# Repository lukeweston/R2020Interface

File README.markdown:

CAN interface board for Rutex R2020 servo controller   

// Rest of readme goes here.

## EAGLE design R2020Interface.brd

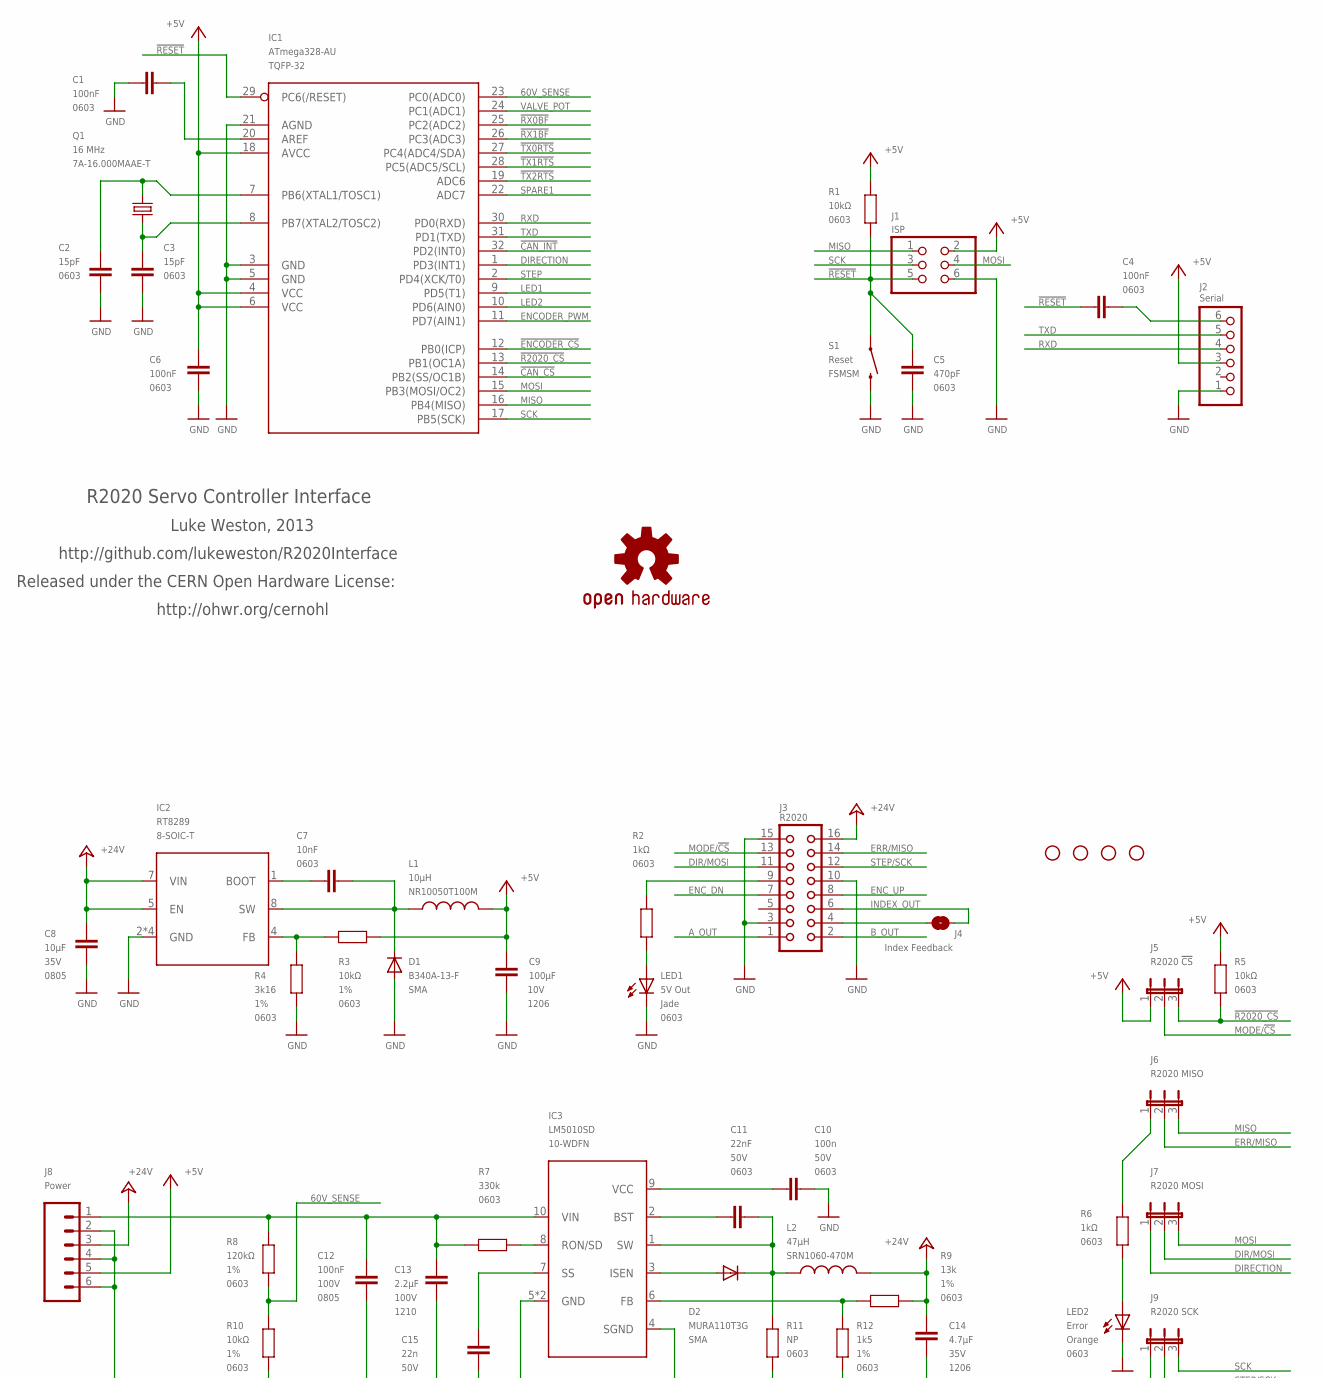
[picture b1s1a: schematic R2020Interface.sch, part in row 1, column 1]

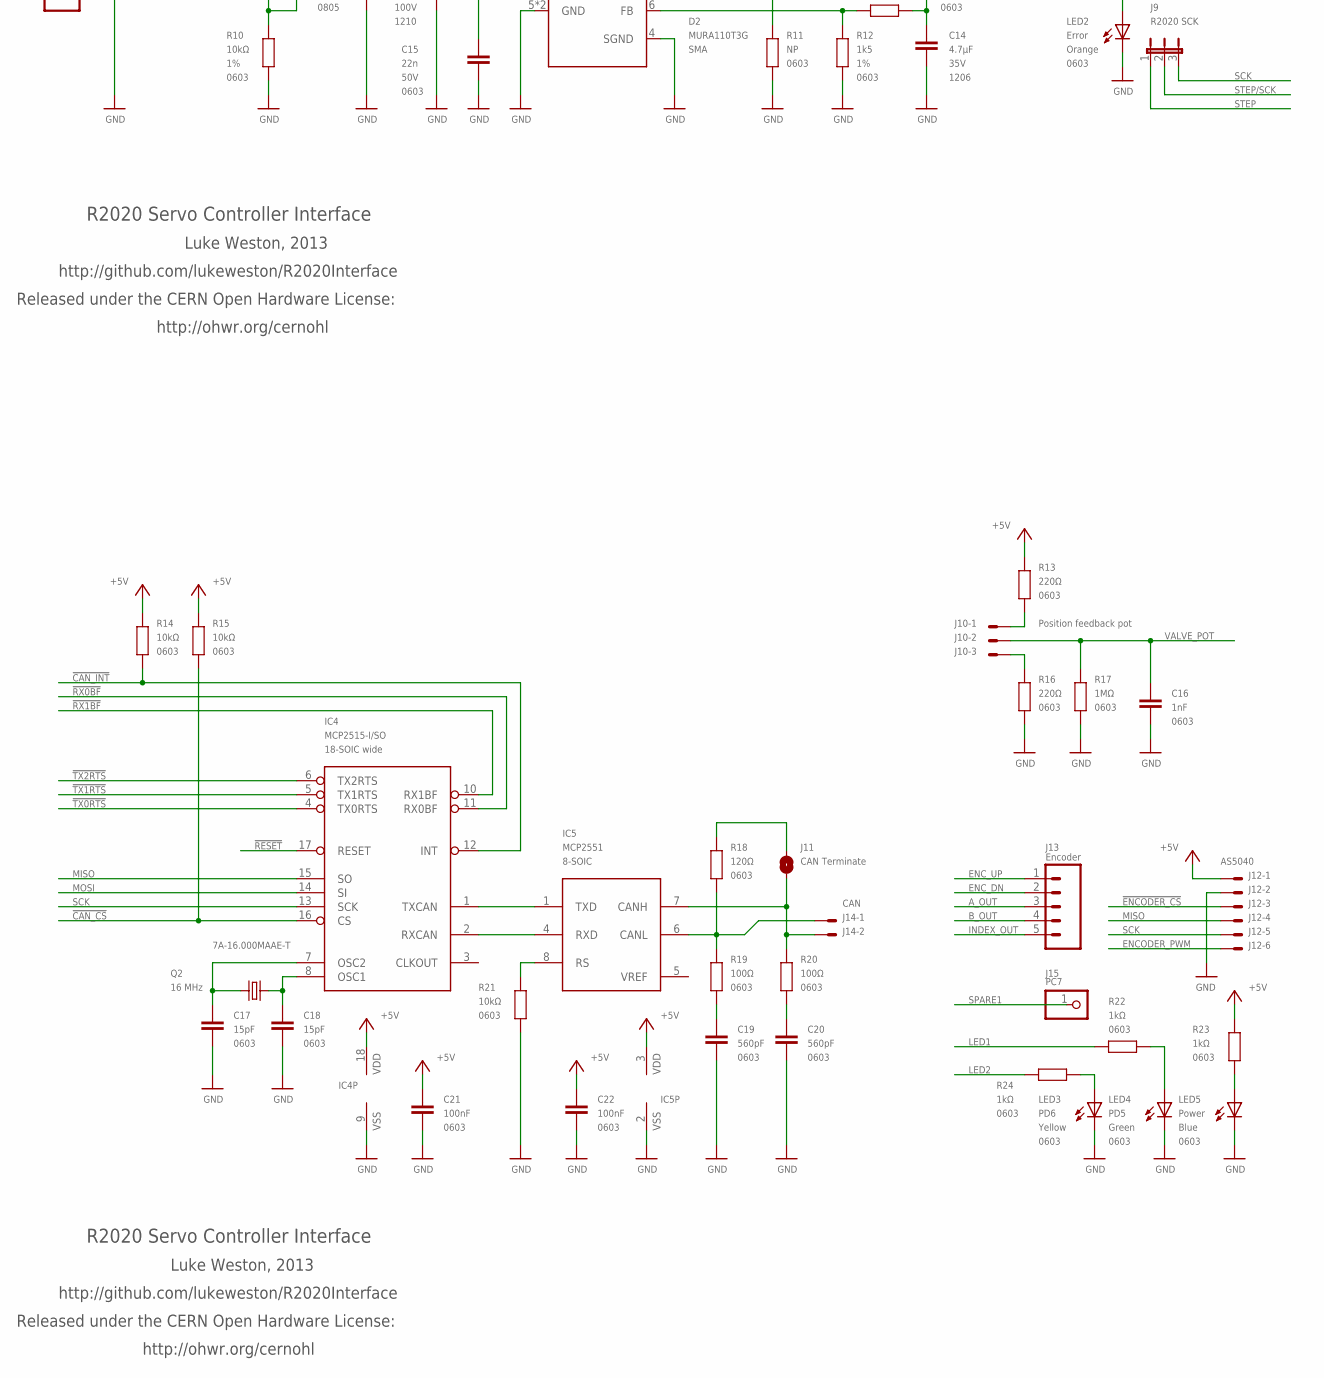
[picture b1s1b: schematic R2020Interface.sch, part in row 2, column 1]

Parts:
C1, C4, C6, C21, C22: 100nF; 0603
C2, C3, C17, C18: 15pF; 0603
C5: 470pF; 0603
C7: 10nF; 0603
C8: 10µF; 0805; VOLTAGE 35V
C9: 100µF; C1206K; VOLTAGE 10V
C10: 100n; 0603; VOLTAGE 50V
C11: 22nF; 0603; VOLTAGE 50V
C12: 100nF; 0805; VOLTAGE 100V
C13: 2.2µF; C1210K; VOLTAGE 100V
C14: 4.7µF; C1206K; VOLTAGE 35V
C15: 22n; 0603; VOLTAGE 50V
C16: 1nF; 0603
C19, C20: 560pF; 0603
D1: B340A-13-F; SMA-DIODE
D2: MURA110T3G; SMA-DIODE
IC1: ATmega328-AU; TQFP32-08
IC2: RT8289; SO08T
IC3: LM5010SD; 10-WSON
IC4: MCP2515-I/SO; SO-18W
IC5: MCP2551; SO-08
J1: ISP; 2X03
J2: Serial; 1X06
J3: R2020; CON16
J4: Index Feedback; SJ
J5: R2020 !CS; JP2
J6: R2020 MISO; JP2
J7: R2020 MOSI; JP2
J8: Power; TERMINALBLOCK_3.5MM_6
J9: R2020 SCK; JP2
J10: Position feedback pot; 7395-03
J11: CAN Terminate; SJ
J12: AS5040; 7395-06
J13: Encoder; 1X05
J14: CAN; 7395-02
J15: PC7; 1X01
JP1, JP2, JP3, JP4: STAND-OFF
L1: 10µH; NR10050
L2: 47µH; SRN1060
LED1: 5V Out; LED-0603
LED2: Error; LED-0603
LED3: PD6; LED-0603
LED4: PD5; LED-0603
LED5: Power; LED-0603
Q1, Q2: 16 MHz; CRYSTAL-3.2X5MM
R1, R5, R14, R15, R21: 10kΩ; 0603
R2, R6, R22, R23, R24: 1kΩ; 0603
R3, R10: 10kΩ; 0603; TOLERANCE 1%
R4: 3k16; 0603; TOLERANCE 1%
R7: 330k; 0603
R8: 120kΩ; 0603; TOLERANCE 1%
R9: 13k; 0603; TOLERANCE 1%
R11: NP; 0603
R12: 1k5; 0603; TOLERANCE 1%
R13, R16: 220Ω; 0603
R17: 1MΩ; 0603
R18: 120Ω; 0603
R19, R20: 100Ω; 0603
S1: Reset; FSMSM
SY1: OSHW-LOGOS; OSHW-LOGO-S

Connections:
60V_SENSE: IC1.23 (PC0(ADC0)), R8.1, R10.2
!CAN_CS: IC1.14 (PB2(SS/OC1B)), IC4.16 (CS), R15.2
!CAN_INT: IC1.32 (PD2(INT0)), IC4.12 (INT), R14.2
!ENCODER_CS: IC1.12 (PB0(ICP)), J12.3
!R2020_CS: IC1.13 (PB1(OC1A)), J5.3, R5.2
!RESET: C4.1, C5.2, IC1.29 (PC6(/RESET)), IC4.17 (RESET), J1.5, R1.1, S1.1
!RX0BF: IC1.25 (PC2(ADC2)), IC4.11 (RX0BF)
!RX1BF: IC1.26 (PC3(ADC3)), IC4.10 (RX1BF)
!TX0RTS: IC1.27 (PC4(ADC4/SDA)), IC4.4 (TX0RTS)
!TX1RTS: IC1.28 (PC5(ADC5/SCL)), IC4.5 (TX1RTS)
!TX2RTS: IC1.19 (ADC6), IC4.6 (TX2RTS)
+5V: C6.1, C9.1, C21.2, C22.2, IC1.4 (VCC), IC1.6 (VCC), IC1.18 (AVCC), IC4.18 (VDD), IC5.3 (VDD), J1.2, J2.3, J5.1, J8.5, J12.1, L1.2, R1.2, R3.1, R5.1, R13.1, R14.1, R15.1, R23.1
+24V: C8.2, C14.1, IC2.5 (EN), IC2.7 (VIN), J3.16, J8.3, L2.2, R9.1
A_OUT: J3.1, J13.3
B_OUT: J3.2, J13.4
DIR/MOSI: J3.11, J7.2
DIRECTION: IC1.1 (PD3(INT1)), J7.1
ENCODER_PWM: IC1.11 (PD7(AIN1)), J12.6
ENC_DN: J3.7, J13.2
ENC_UP: J3.8, J13.1
ERR/MISO: J3.14, J6.2
GND: C1.2, C2.1, C3.1, C5.1, C6.2, C8.1, C9.2, C10.1, C12.1, C13.2, C14.2, C15.1, C16.1, C17.1, C18.1, C19.1, C20.1, C21.1, C22.1, D1.A, IC1.3 (GND), IC1.5 (GND), IC1.21 (AGND), IC2.2 (GND), IC2.3 (GND), IC2.6 (GND), IC2.PAD (GND), IC3.4 (SGND), IC3.5 (GND), IC3.PAD (GND), IC4.9 (VSS), IC5.2 (VSS), J1.6, J2.1, J3.3, J3.10, J3.15, J8.2, J8.4, J8.6, J12.2, LED1.C, LED2.C, LED3.C, LED4.C, LED5.C, R4.1, R10.1, R11.2, R12.1, R16.2, R17.2, R21.2, S1.2
INDEX_IN: J3.4, J4.2
INDEX_OUT: J3.6, J4.1, J13.5
LED1: IC1.9 (PD5(T1)), R22.2
LED2: IC1.10 (PD6(AIN0)), R24.2
MISO: IC1.16 (PB4(MISO)), IC4.15 (SO), J1.1, J6.3, J12.4
MODE/!CS: J3.13, J5.2
MOSI: IC1.15 (PB3(MOSI/OC2)), IC4.14 (SI), J1.4, J7.3
unnamed: C1.1, IC1.20 (AREF)
unnamed: C2.2, IC1.7 (PB6(XTAL1/TOSC1)), Q1.1
unnamed: C3.2, IC1.8 (PB7(XTAL2/TOSC2)), Q1.2
unnamed: LED1.A, R2.1
unnamed: J3.9, R2.2
unnamed: J10.1, R13.2
unnamed: J6.1, R6.1
unnamed: J11.2, R18.1
unnamed: J10.3, R16.1
unnamed: LED2.A, R6.2
unnamed: C7.1, D1.C, IC2.8 (SW), L1.1
unnamed: IC5.7 (CANH), J11.1, J14.2, R20.1
unnamed: LED3.A, R24.1
unnamed: IC2.4 (FB), R3.2, R4.2
unnamed: LED4.A, R22.1
unnamed: C7.2, IC2.1 (BOOT)
unnamed: C11.1, D2.C, IC3.1 (SW), L2.1, R11.1
unnamed: IC5.8 (RS), R21.1
unnamed: D2.A, IC3.3 (ISEN)
unnamed: IC3.6 (FB), R9.2, R12.2
unnamed: C15.2, IC3.7 (SS)
unnamed: IC3.8 (RON/SD), R7.1
unnamed: IC4.2 (RXCAN), IC5.4 (RXD)
unnamed: IC4.1 (TXCAN), IC5.1 (TXD)
unnamed: C10.2, IC3.9 (VCC)
unnamed: C4.2, J2.6
unnamed: C11.2, IC3.2 (BST)
unnamed: LED5.A, R23.2
unnamed: C19.2, R19.2
unnamed: C20.2, R20.2
unnamed: IC5.6 (CANL), J14.1, R18.2, R19.1
unnamed: C12.2, C13.1, IC3.10 (VIN), J8.1, R7.2, R8.2
unnamed: C18.2, IC4.8 (OSC1), Q2.1
unnamed: C17.2, IC4.7 (OSC2), Q2.2
RXD: IC1.30 (PD0(RXD)), J2.4
SCK: IC1.17 (PB5(SCK)), IC4.13 (SCK), J1.3, J9.3, J12.5
SPARE1: IC1.22 (ADC7), J15.1
STEP: IC1.2 (PD4(XCK/T0)), J9.1
STEP/SCK: J3.12, J9.2
TXD: IC1.31 (PD1(TXD)), J2.5
VALVE_POT: C16.2, IC1.24 (PC1(ADC1)), J10.2, R17.1
VREF: IC5.5 (VREF)

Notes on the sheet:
R2020 Servo Controller Interface
Luke Weston, 2013
http://github.com/lukeweston/R2020Interface
Released under the CERN Open Hardware License:
http://ohwr.org/cernohl

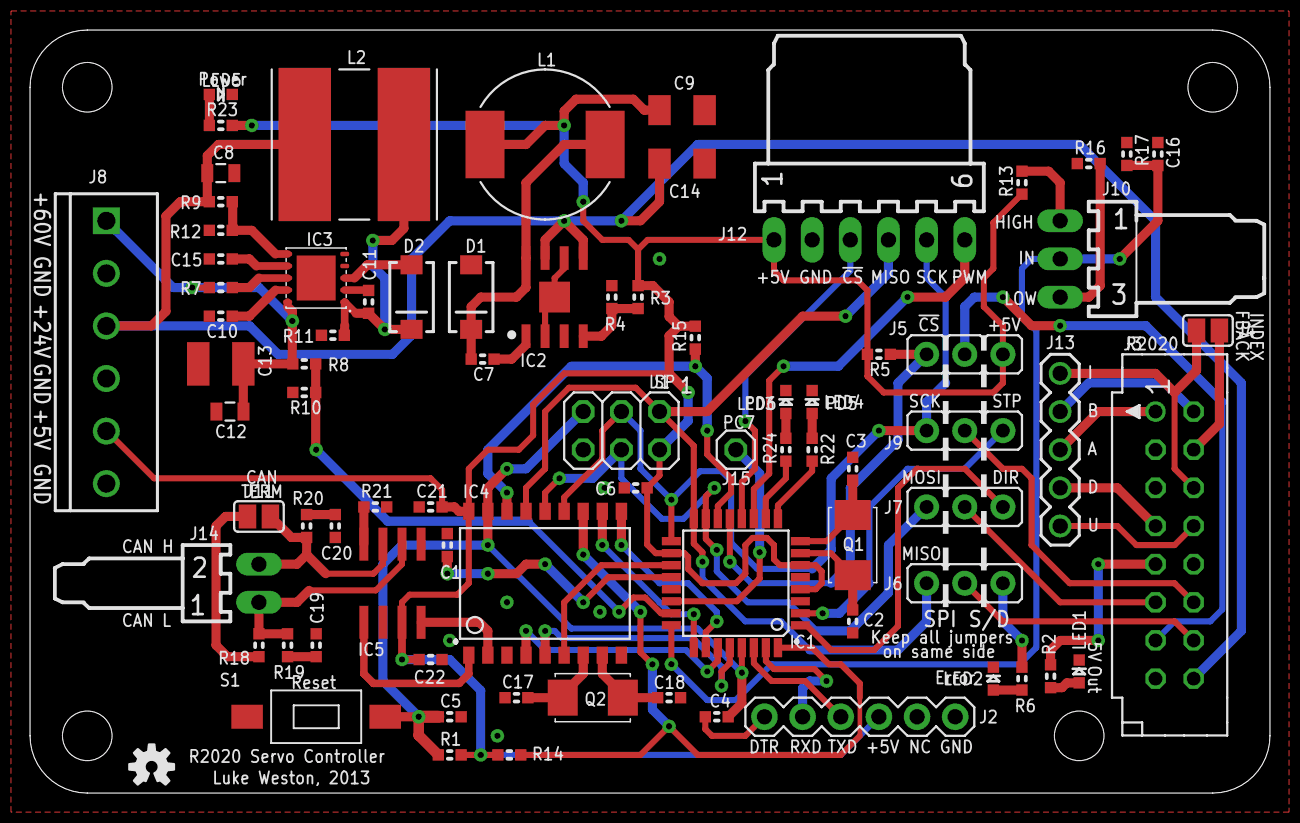
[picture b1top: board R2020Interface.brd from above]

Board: 2 copper layers, 82.5 x 50.8 mm, 83 parts (0 on the bottom side), 70 nets.

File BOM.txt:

R1, R3, R5, R10, R14, R15, R21:	10k 1%, 0603 SMD
R2, R6, R22, R23, R24:		1k, 0603 SMD
R13, R16:			220 ohm, 0603 SMD
R19, R20:			100 ohm, 0603 SMD
R4:				3k16 1%, 0603 SMD
R7:				330k, 0603 SMD
R8:				120k 1%, 0603 SMD
R9:				13k0 1%, 0603 SMD
R12:				1k5 1%, 0603 SMD
R17:				1M, 0603 SMD
R18:				120 ohm, 0603 SMD
R11:				NP

C1, C4, C6, C10, C21, C22:	100nF ceramic, 50V, 0603 package.
C2, C3, C17, C18:		15pF ceramic, 0603 package.
C19, C20:			560pF ceramic, 0603 package.
C5:				470pF ceramic, 0603 package.
C7:				10nF ceramic, 0603 package.
C8:				10uF 35V ceramic, 0805 SMD package.
C9:				100uF 10V ceramic, 1206 SMD package.
C11:				22nF 50V ceramic, 0603 SMD package.
C12:				100nF 100V ceramic, 0805 SMD package.
C13:				2.2uF 100V ceramic, 1210 SMD package.
C14:				4.7uF 35V ceramic, 1206 SMD package.
C15:				22nF 50V ceramic, 0603 SMD package.
C16:				1nF 50V ceramic, 0603 SMD package.

D1:				B340A-13-F, SMA package
D2:				MURA110T3G, SMA package

LED1:				0603 LED, jade
LED2:				0603 LED, orange
LED3:				0603 LED, yellow
LED4:				0603 LED, green
LED5:				0603 LED, blue

IC1				ATmega328-AU, 32-TQFN
IC2				RT8289, SOIC8T
IC3				LM5010SD, 10-WSON
IC4				MCP2515-I/SO, 18-SOIC wide
IC5				MCP2551, 8-SOIC
Q1, Q2:				16 MHz crystal, 3.2x5mm, TXC 7A-16.000MAAE-T
L1:				10uH SMD inductor, Taiyo Yuden NR10050T100M
L2:				47uH SMD inductor, Bourns SRN1060-470M

S1:				2-pin momentary tactile pushbutton, SMD.
J1:				2x3 0,1" pin header
J2:				1x6 0.1" pin header
J3:				16-pin IDC box header
J5, J6, J7, J9:			3-pin 0.1" pin header
J8:				6-pin 3.5mm PCB screw terminal block
J10:		 		3-pin 0.1" right-angle Molex KK header
J12:				6-pin 0.1" right-angle Molex KK header
J14:				2-pin 0.1" right-angle Molex KK header
J4, J11, J13, J15:		NP

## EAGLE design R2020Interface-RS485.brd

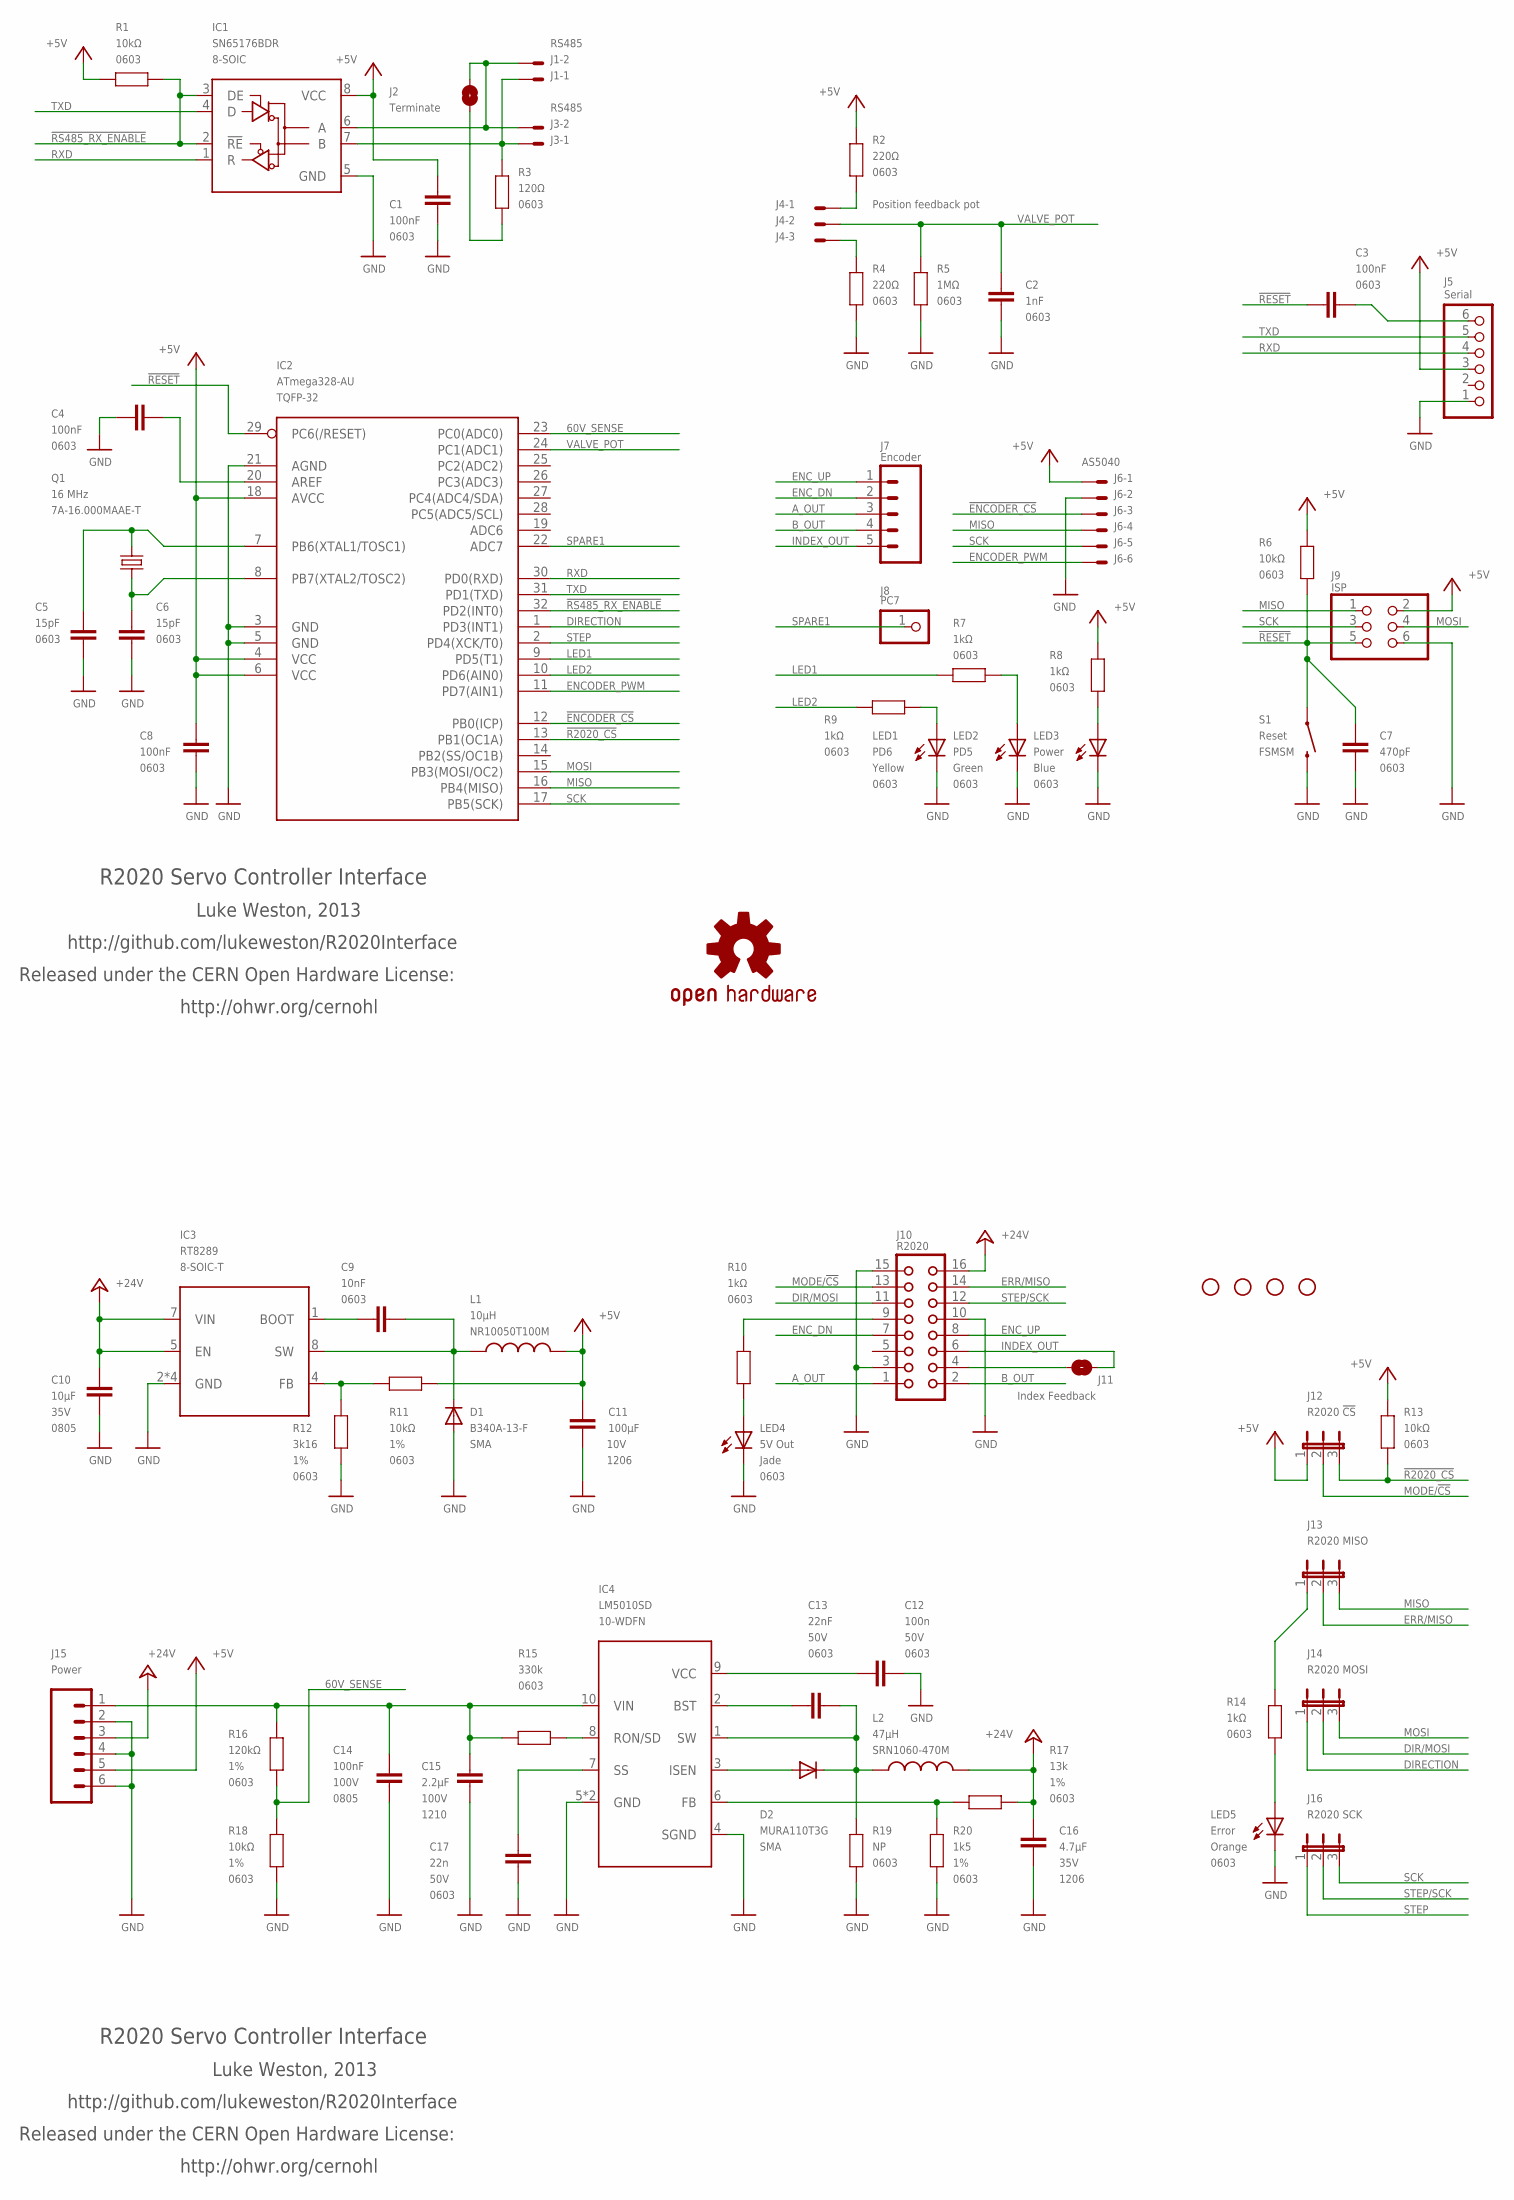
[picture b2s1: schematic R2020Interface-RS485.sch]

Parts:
C1, C3, C4, C8: 100nF; 0603
C2: 1nF; 0603
C5, C6: 15pF; 0603
C7: 470pF; 0603
C9: 10nF; 0603
C10: 10µF; 0805; VOLTAGE 35V
C11: 100µF; C1206K; VOLTAGE 10V
C12: 100n; 0603; VOLTAGE 50V
C13: 22nF; 0603; VOLTAGE 50V
C14: 100nF; 0805; VOLTAGE 100V
C15: 2.2µF; C1210K; VOLTAGE 100V
C16: 4.7µF; C1206K; VOLTAGE 35V
C17: 22n; 0603; VOLTAGE 50V
D1: B340A-13-F; SMA-DIODE
D2: MURA110T3G; SMA-DIODE
IC1: SN65176BDR; D_R-PDSO-G8
IC2: ATmega328-AU; TQFP32-08
IC3: RT8289; SO08T
IC4: LM5010SD; 10-WSON
J1, J3: RS485; 7395-02
J2: Terminate; SJ
J4: Position feedback pot; 7395-03
J5: Serial; 1X06
J6: AS5040; 7395-06
J7: Encoder; 1X05
J8: PC7; 1X01
J9: ISP; 2X03
J10: R2020; CON16
J11: Index Feedback; SJ
J12: R2020 !CS; JP2
J13: R2020 MISO; JP2
J14: R2020 MOSI; JP2
J15: Power; TERMINALBLOCK_3.5MM_6
J16: R2020 SCK; JP2
JP1, JP2, JP3, JP4: STAND-OFF
L1: 10µH; NR10050
L2: 47µH; SRN1060
LED1: PD6; LED-0603
LED2: PD5; LED-0603
LED3: Power; LED-0603
LED4: 5V Out; LED-0603
LED5: Error; LED-0603
Q1: 16 MHz; CRYSTAL-3.2X5MM
R1, R6, R13: 10kΩ; 0603
R2, R4: 220Ω; 0603
R3: 120Ω; 0603
R5: 1MΩ; 0603
R7, R8, R9, R10, R14: 1kΩ; 0603
R11, R18: 10kΩ; 0603; TOLERANCE 1%
R12: 3k16; 0603; TOLERANCE 1%
R15: 330k; 0603
R16: 120kΩ; 0603; TOLERANCE 1%
R17: 13k; 0603; TOLERANCE 1%
R19: NP; 0603
R20: 1k5; 0603; TOLERANCE 1%
S1: Reset; FSMSM
SY1: OSHW-LOGOS; OSHW-LOGO-S

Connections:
60V_SENSE: IC2.23 (PC0(ADC0)), R16.1, R18.2
!ENCODER_CS: IC2.12 (PB0(ICP)), J6.3
!R2020_CS: IC2.13 (PB1(OC1A)), J12.3, R13.2
!RESET: C3.1, C7.2, IC2.29 (PC6(/RESET)), J9.5, R6.1, S1.1
!RS485_RX_ENABLE: IC1.2 (!RE), IC1.3 (DE), IC2.32 (PD2(INT0)), R1.2
+5V: C1.2, C8.1, C11.1, IC1.8 (VCC), IC2.4 (VCC), IC2.6 (VCC), IC2.18 (AVCC), J5.3, J6.1, J9.2, J12.1, J15.5, L1.2, R1.1, R2.1, R6.2, R8.1, R11.1, R13.1
+24V: C10.2, C16.1, IC3.5 (EN), IC3.7 (VIN), J10.16, J15.3, L2.2, R17.1
A_OUT: J7.3, J10.1
B_OUT: J7.4, J10.2
DIR/MOSI: J10.11, J14.2
DIRECTION: IC2.1 (PD3(INT1)), J14.1
ENCODER_PWM: IC2.11 (PD7(AIN1)), J6.6
ENC_DN: J7.2, J10.7
ENC_UP: J7.1, J10.8
ERR/MISO: J10.14, J13.2
GND: C1.1, C2.1, C4.2, C5.1, C6.1, C7.1, C8.2, C10.1, C11.2, C12.1, C14.1, C15.2, C16.2, C17.1, D1.A, IC1.5 (GND), IC2.3 (GND), IC2.5 (GND), IC2.21 (AGND), IC3.2 (GND), IC3.3 (GND), IC3.6 (GND), IC3.PAD (GND), IC4.4 (SGND), IC4.5 (GND), IC4.PAD (GND), J5.1, J6.2, J9.6, J10.3, J10.10, J10.15, J15.2, J15.4, J15.6, LED1.C, LED2.C, LED3.C, LED4.C, LED5.C, R4.2, R5.2, R12.1, R18.1, R19.2, R20.1, S1.2
INDEX_IN: J10.4, J11.2
INDEX_OUT: J7.5, J10.6, J11.1
LED1: IC2.9 (PD5(T1)), R7.2
LED2: IC2.10 (PD6(AIN0)), R9.2
MISO: IC2.16 (PB4(MISO)), J6.4, J9.1, J13.3
MODE/!CS: J10.13, J12.2
MOSI: IC2.15 (PB3(MOSI/OC2)), J9.4, J14.3
unnamed: C4.1, IC2.20 (AREF)
unnamed: C5.2, IC2.7 (PB6(XTAL1/TOSC1)), Q1.1
unnamed: C6.2, IC2.8 (PB7(XTAL2/TOSC2)), Q1.2
unnamed: LED4.A, R10.1
unnamed: J10.9, R10.2
unnamed: J4.1, R2.2
unnamed: J13.1, R14.1
unnamed: IC1.6 (A), J1.2, J2.2, J3.2
unnamed: J4.3, R4.1
unnamed: LED5.A, R14.2
unnamed: C9.1, D1.C, IC3.8 (SW), L1.1
unnamed: IC1.7 (B), J1.1, J3.1, R3.1
unnamed: LED1.A, R9.1
unnamed: IC3.4 (FB), R11.2, R12.2
unnamed: LED2.A, R7.1
unnamed: C9.2, IC3.1 (BOOT)
unnamed: C13.1, D2.C, IC4.1 (SW), L2.1, R19.1
unnamed: J2.1, R3.2
unnamed: D2.A, IC4.3 (ISEN)
unnamed: IC4.6 (FB), R17.2, R20.2
unnamed: C17.2, IC4.7 (SS)
unnamed: IC4.8 (RON/SD), R15.1
unnamed: C12.2, IC4.9 (VCC)
unnamed: C3.2, J5.6
unnamed: C13.2, IC4.2 (BST)
unnamed: LED3.A, R8.2
unnamed: C14.2, C15.1, IC4.10 (VIN), J15.1, R15.2, R16.2
RXD: IC1.1 (R), IC2.30 (PD0(RXD)), J5.4
SCK: IC2.17 (PB5(SCK)), J6.5, J9.3, J16.3
SPARE1: IC2.22 (ADC7), J8.1
STEP: IC2.2 (PD4(XCK/T0)), J16.1
STEP/SCK: J10.12, J16.2
TXD: IC1.4 (D), IC2.31 (PD1(TXD)), J5.5
VALVE_POT: C2.2, IC2.24 (PC1(ADC1)), J4.2, R5.1

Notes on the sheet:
R2020 Servo Controller Interface
Luke Weston, 2013
http://github.com/lukeweston/R2020Interface
Released under the CERN Open Hardware License:
http://ohwr.org/cernohl

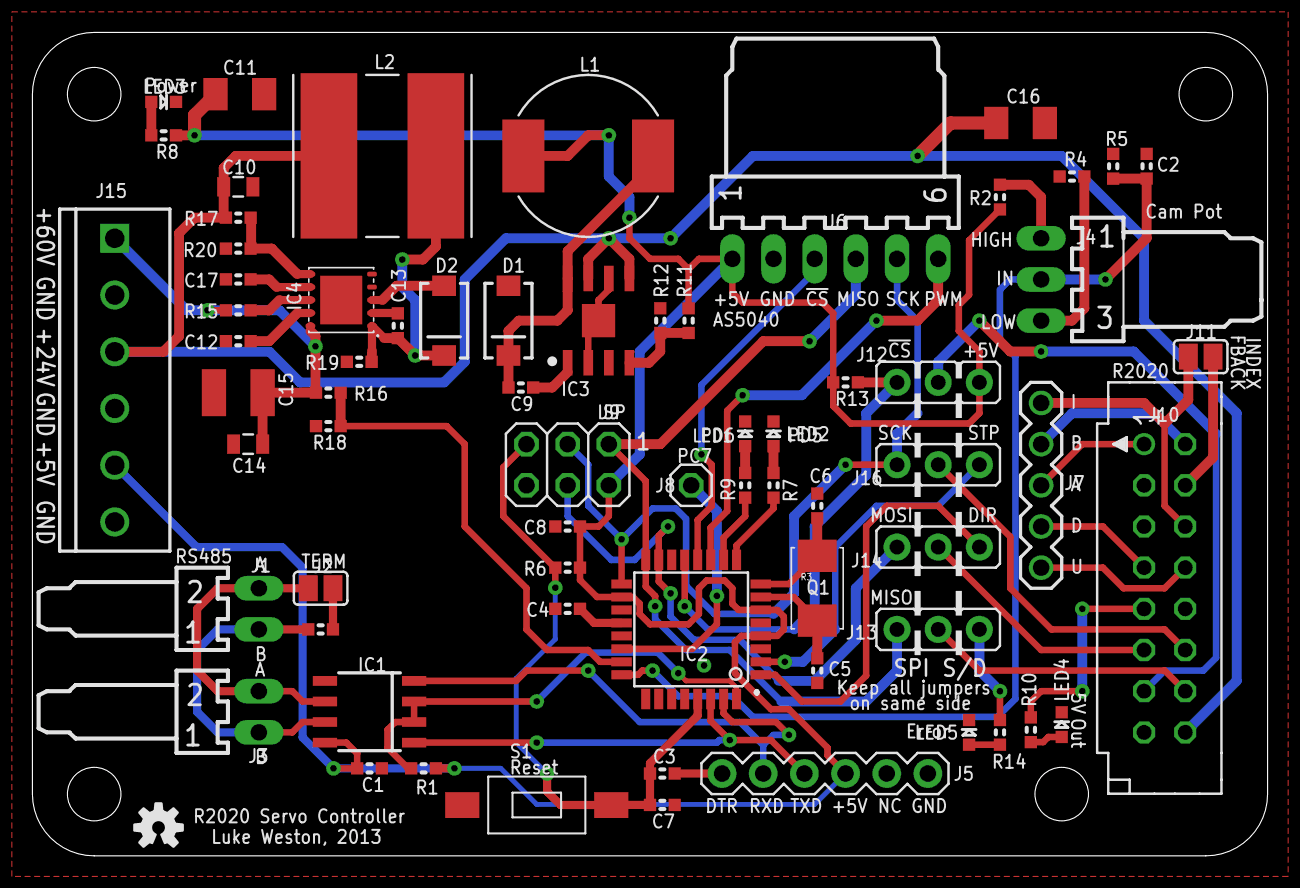
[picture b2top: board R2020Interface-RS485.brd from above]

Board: 2 copper layers, 76.2 x 50.8 mm, 73 parts (0 on the bottom side), 57 nets.

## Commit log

2013-05-26 added image
2013-05-26 added BOM
2013-05-29 added RS485 interfaced version
